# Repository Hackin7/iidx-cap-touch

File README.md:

# iidx-cap-touch
Beatmania IIDX Capacitive Touch Controller

## PCB 2

Usage
1. Connect 1 MPR121 to a RPi Pico
    - Can extend with an additional MPR121 port
2. Top left (thin) pad can act as turntable button - Or you can use PCB 1 with an additional MPR121 for a turntable
3. CircuitPython on the RPi Pico allows you to configure keybindings
4. Should Tapedown the controller to prevent sliding - cap touch + pcb + tapedown = minimal noise

Ordering
1. Both PCBs in the picture are using the same design - Can order 1 pack of 5 for $2 + $2 for 2 weeks shipping
2. Connect them together through headers/ wires

## PCB 1

1. Connect 2 MPR121 to a Raspberry Pi Pico, each on different I2C buses
2. CircuitPython Code to simulate a turntable (still a bit wonky, but usable for simple maps)
3. PCB controller for ease of use. 5 costs $2 + $2 shipping in 10 days or so.

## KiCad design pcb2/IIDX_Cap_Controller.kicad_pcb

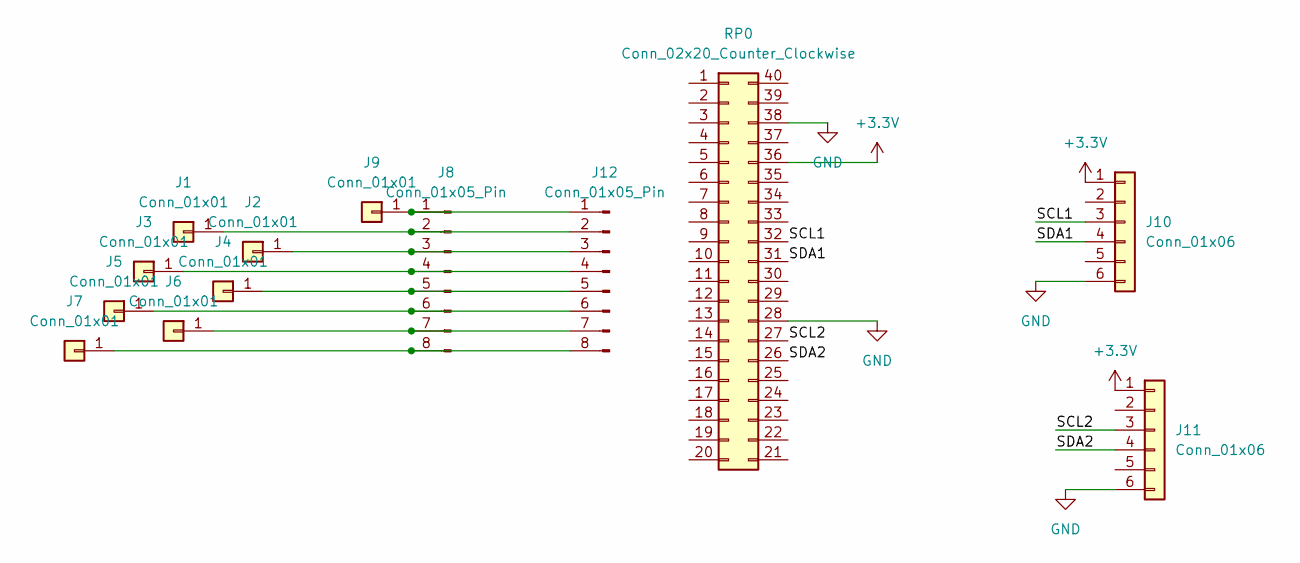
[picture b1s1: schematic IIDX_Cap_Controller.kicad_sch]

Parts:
J1, J2, J3, J4, J5, J6, J7, J9: Conn_01x01; 4807e8d7-bff8-4c85-8422-397af0b06065
J8: Conn_01x05_Pin; PinHeader_1x08_P2.54mm_Vertical
J10: Conn_01x06; PinHeader_1x06_P2.54mm_Vertical
J11: Conn_01x06
J12: Conn_01x05_Pin; PinHeader_1x08_P2.54mm_Vertical_SMD_Pin1Left
RP0: Conn_02x20_Counter_Clockwise

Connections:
+3.3V: J10.1, J11.1, RP0.36
/SCL1: J10.3, RP0.32
/SCL2: J11.3, RP0.27
/SDA1: J10.4, RP0.31
/SDA2: J11.4, RP0.26
GND: J10.6, J11.6, RP0.28, RP0.38
unnamed: J1.1, J8.2, J12.2
unnamed: J8.1, J9.1, J12.1
unnamed: J2.1, J8.3, J12.3
unnamed: J3.1, J8.4, J12.4
unnamed: J4.1, J8.5, J12.5
unnamed: J5.1, J8.6, J12.6
unnamed 12: J6.1, J8.7, J12.7; also elsewhere on the board
unnamed: J7.1, J8.8, J12.8

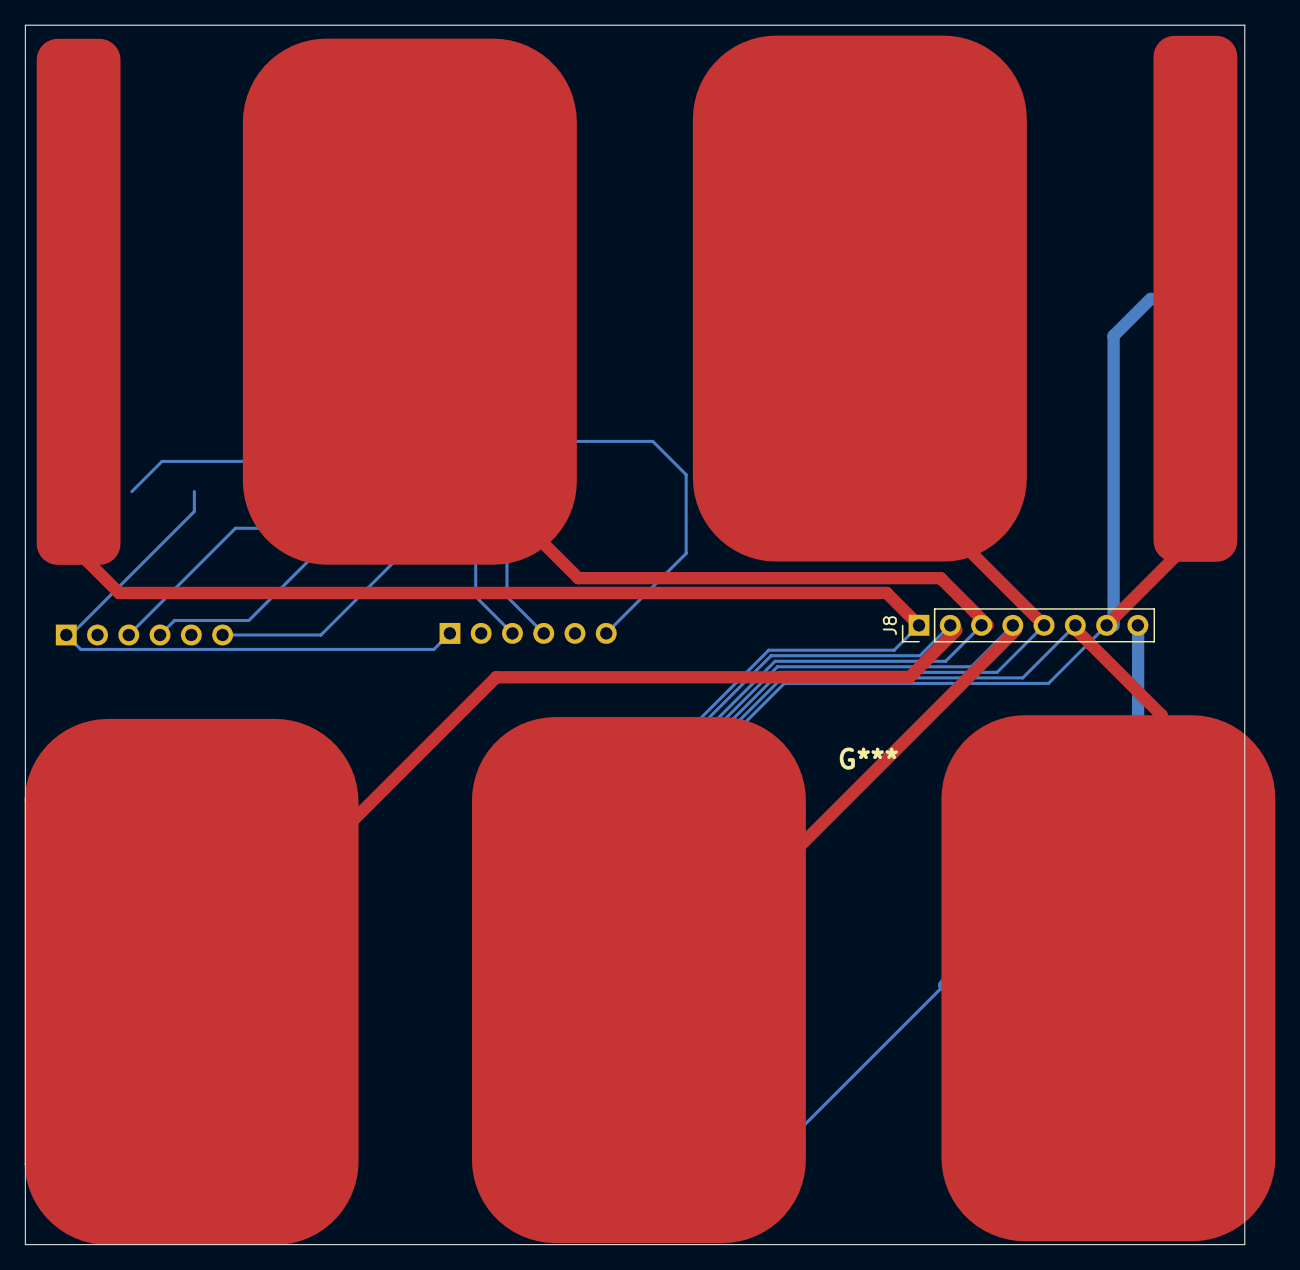
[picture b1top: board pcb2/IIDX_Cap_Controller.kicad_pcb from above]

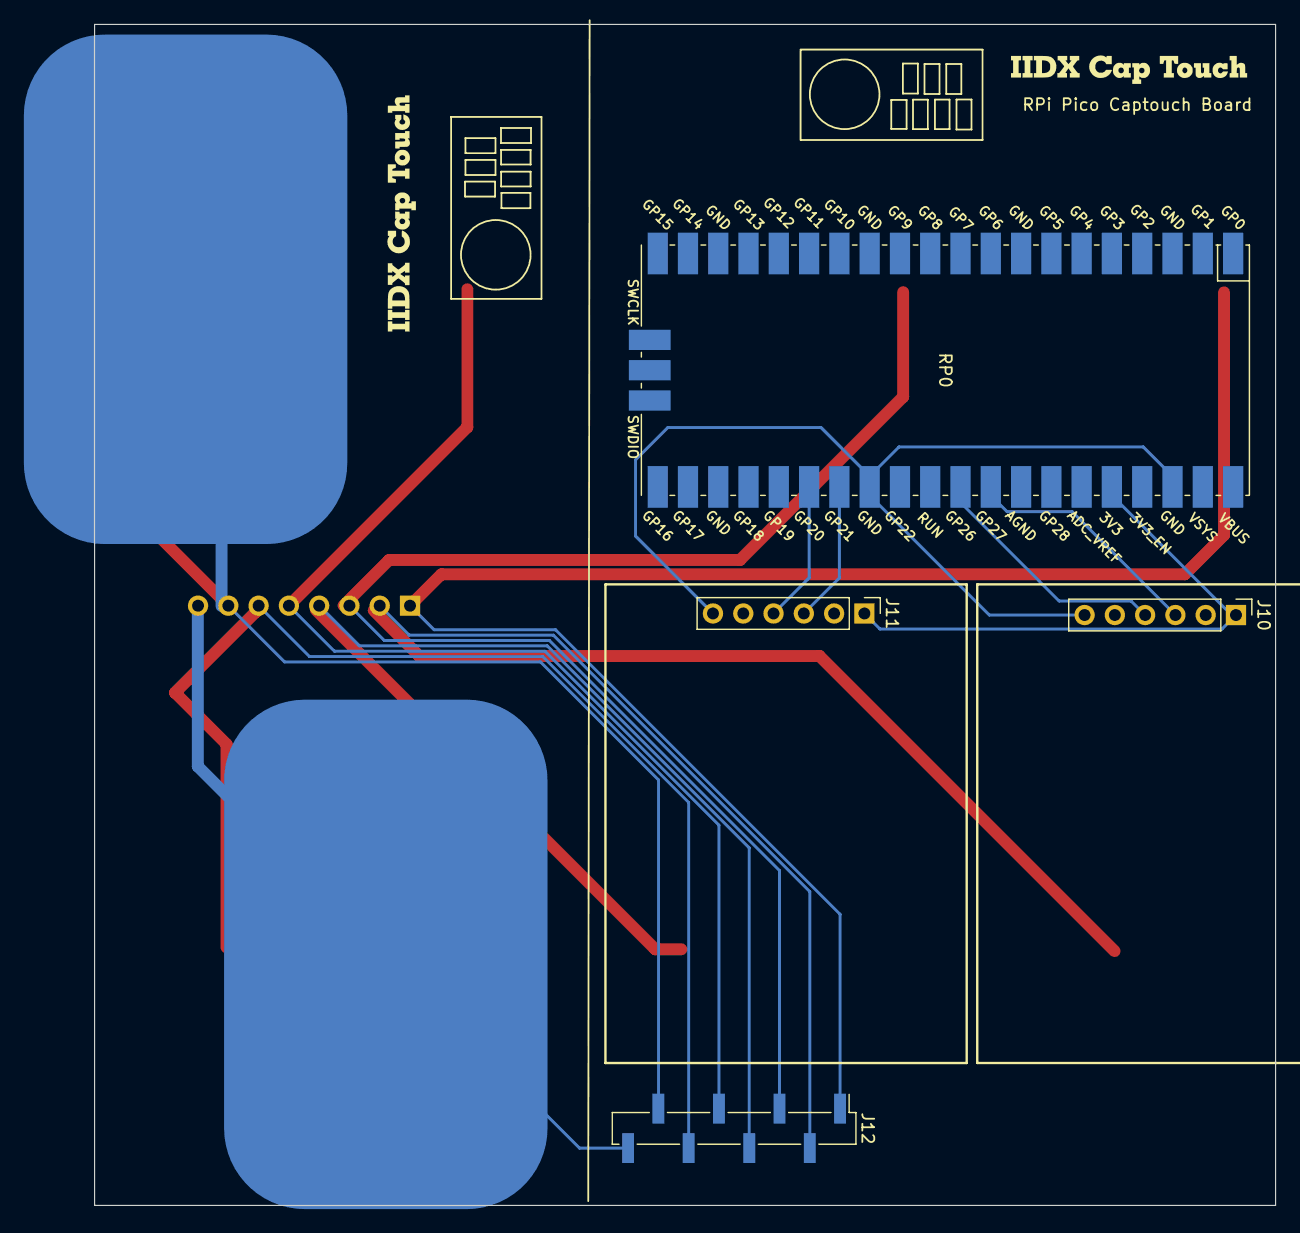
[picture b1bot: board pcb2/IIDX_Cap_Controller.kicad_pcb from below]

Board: 2 copper layers, 99.1 x 99.1 mm, 14 parts (6 on the bottom side), 14 nets.

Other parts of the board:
J6#2: Conn_01x01; 4807e8d7-bff8-4c85-8422-397af0b06065

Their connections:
unnamed 12: J6#2.1; also elsewhere on the board

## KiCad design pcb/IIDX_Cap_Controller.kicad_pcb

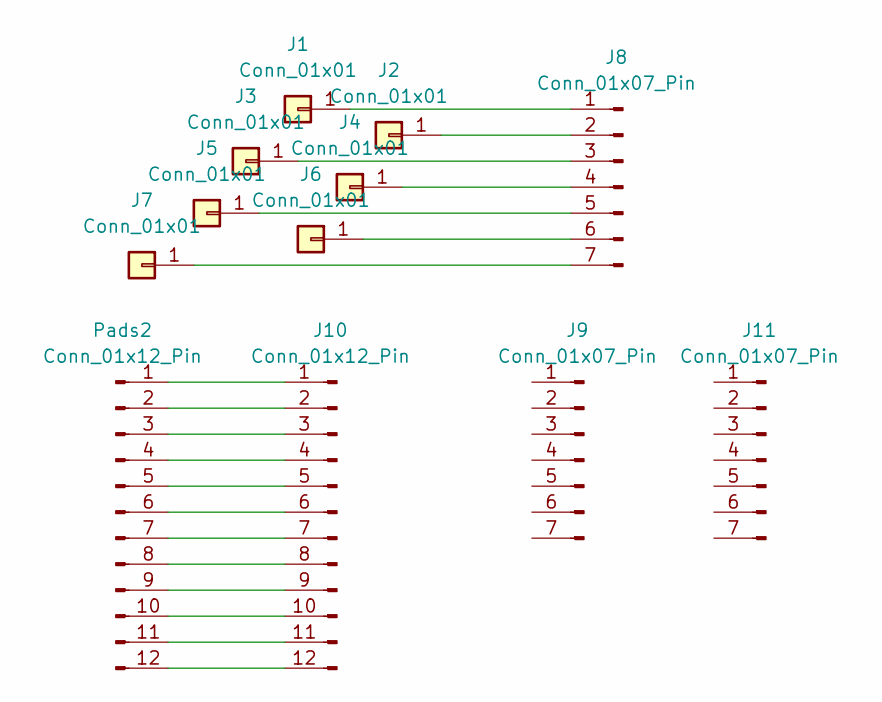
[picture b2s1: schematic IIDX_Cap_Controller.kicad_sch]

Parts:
J1, J2, J3, J4, J5, J6, J7: Conn_01x01; 4807e8d7-bff8-4c85-8422-397af0b06065
J8, J9, J11: Conn_01x07_Pin; PinHeader_1x07_P2.54mm_Vertical
J10: Conn_01x12_Pin
Pads2: Conn_01x12_Pin

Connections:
unnamed: J1.1, J8.1
unnamed: J2.1, J8.2
unnamed: J3.1, J8.3
unnamed: J4.1, J8.4
unnamed: J5.1, J8.5
unnamed: J6.1, J8.6
unnamed: J7.1, J8.7
unnamed: J10.1, Pads2.1
unnamed: J10.2, Pads2.2
unnamed: J10.3, Pads2.3
unnamed: J10.4, Pads2.4
unnamed: J10.5, Pads2.5
unnamed: J10.6, Pads2.6
unnamed: J10.7, Pads2.7
unnamed: J10.8, Pads2.8
unnamed: J10.9, Pads2.9
unnamed: J10.10, Pads2.10
unnamed: J10.11, Pads2.11
unnamed: J10.12, Pads2.12

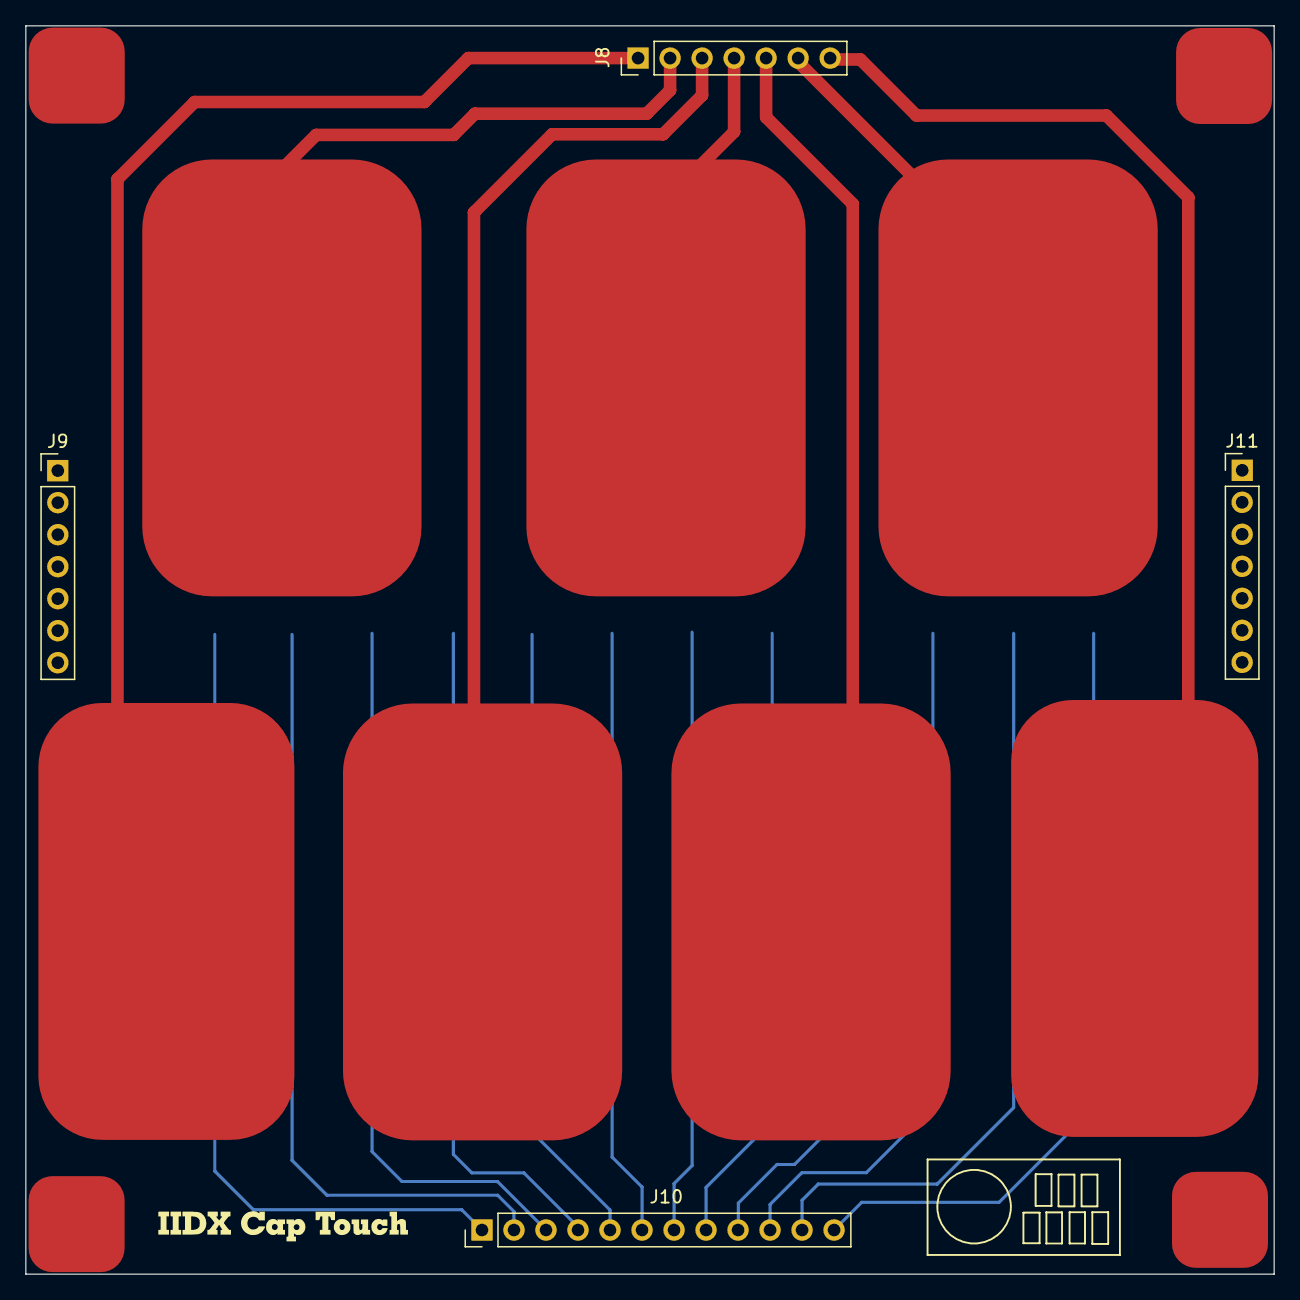
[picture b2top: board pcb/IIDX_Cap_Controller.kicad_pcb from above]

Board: 2 copper layers, 99.1 x 99.1 mm, 16 parts (1 on the bottom side), 19 nets.

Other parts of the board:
SolderJoint: Conn_01x01; 4807e8d7-bff8-4c85-8422-397af0b06065
SolderJoint#2, SolderJoint#3, SolderJoint#4: Conn_01x01; 4807e8d7-bff8-4c85-8422-397af0b06065

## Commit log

2023-09-30 feat: base commit
2023-09-30 chore: cleanup
2024-01-04 feat: pcb2 rough layout
2024-01-05 feat: layout & routing with pico onboard
2024-01-08 feat: production 2
2024-08-05 feat: code update + documentation
